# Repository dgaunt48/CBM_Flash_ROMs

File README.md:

# CBM_Flash_ROMs 
**Various Commodore Cartridge and ROM replacement projects.**

## 16BitFlashROM_Adaptor
Simple adaptor to use a 48 pin SMD flash rom in place of the AMIGA 500 dip rom.
Extra address pins on top to allow selection from multiple rom images.
[link to ibom](ibom_16BitFlashROM_Adaptor.html)

## C64_FlashCart
Flash cartridge for the C64

## FlashCartProgrammer
Flash Cart Programmer with sockets for VIC20 & C64 cartridges plus pin header for programming
of my 16Bit Flash ROM Adaptor board.
[link to ibom](FlashCartProgrammer/ibom.html)

## FlashSPI
Raspberry PI Pico code used to program the SPI Flash ROM on my FPGA boards.

## Vic20_DiagROM
Dissassembly of vc-20-diag.324173-01_blk5.bin.
Source file now assembles back into an identical image of the original Diag ROM file.

## Vic20_FlashCart
Vic20 Ram Expansion and Multi ROM Image Flash Cartridge.
[link to ibom](ibom_Vic20_FlashCart.html)

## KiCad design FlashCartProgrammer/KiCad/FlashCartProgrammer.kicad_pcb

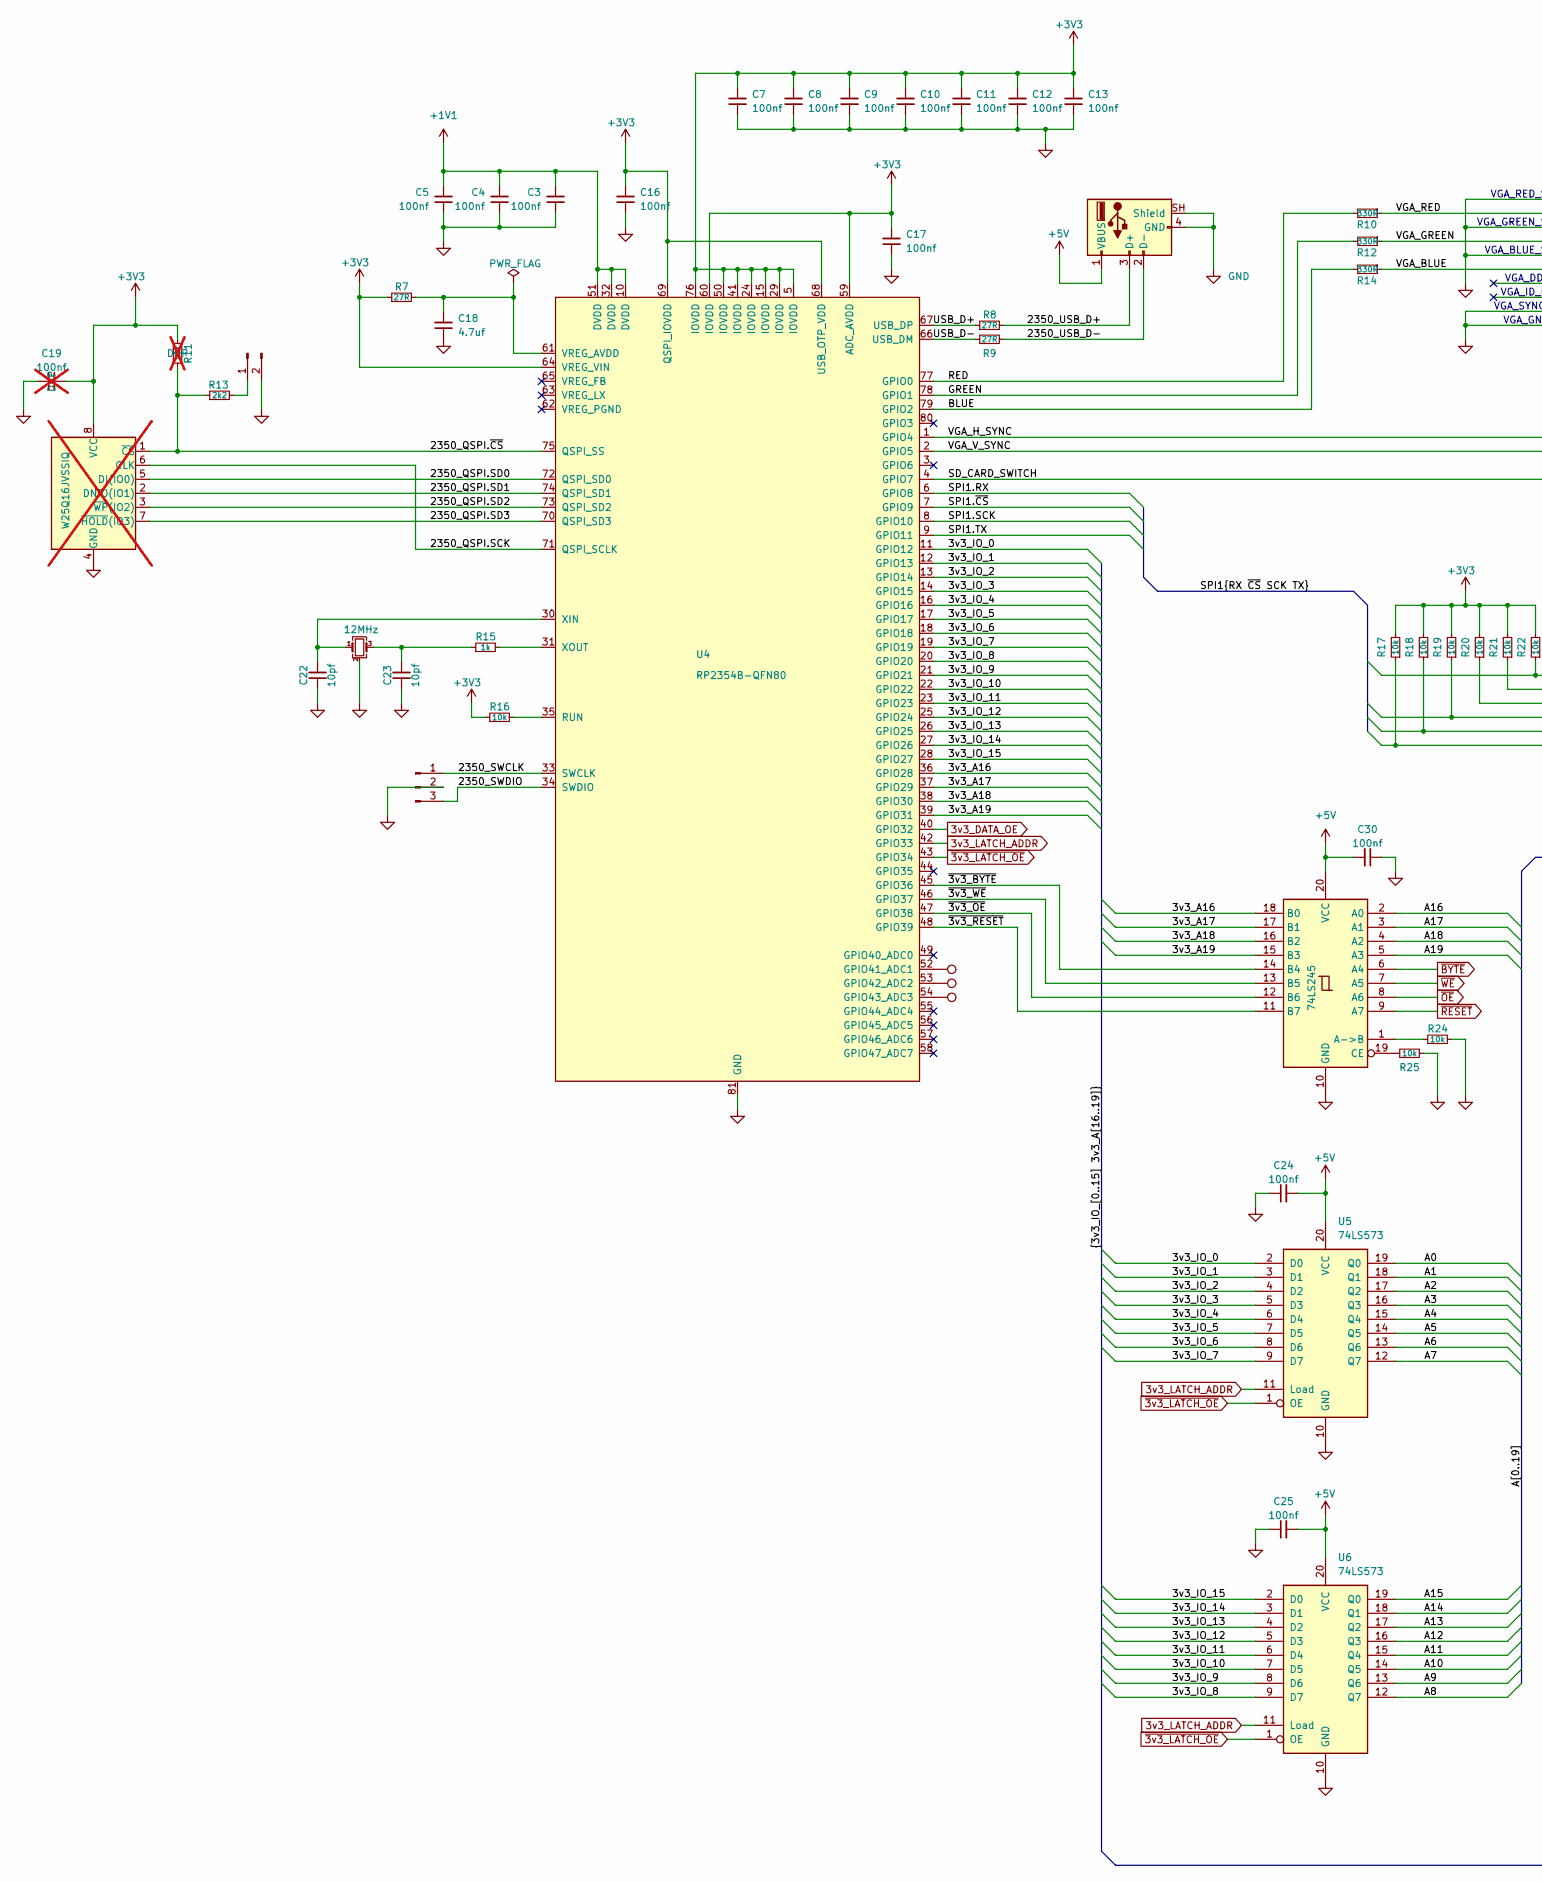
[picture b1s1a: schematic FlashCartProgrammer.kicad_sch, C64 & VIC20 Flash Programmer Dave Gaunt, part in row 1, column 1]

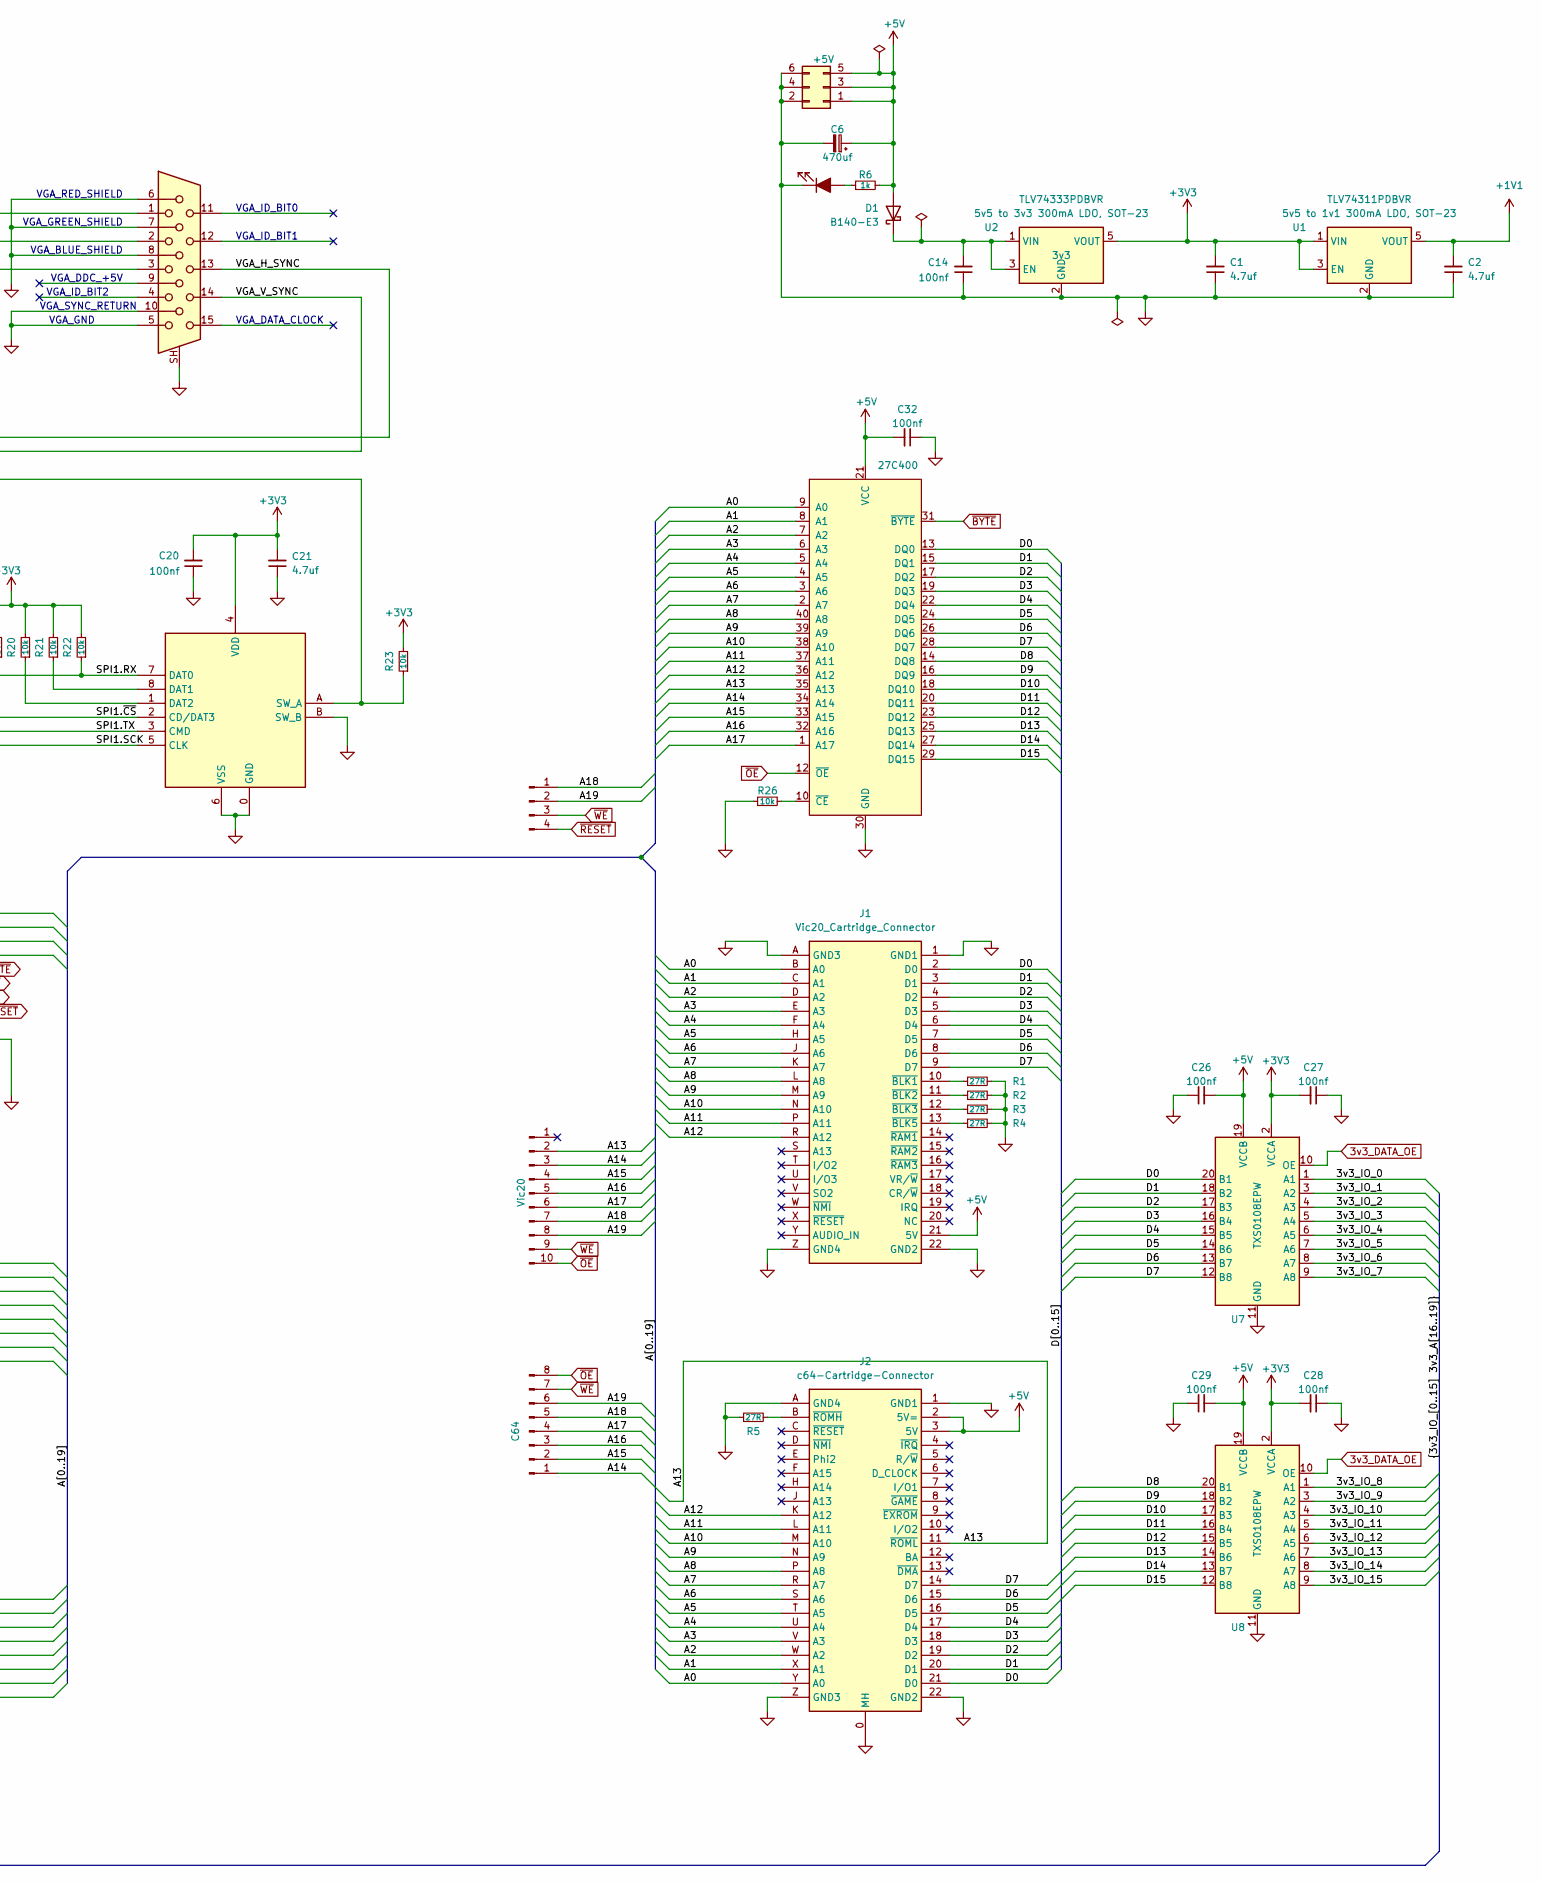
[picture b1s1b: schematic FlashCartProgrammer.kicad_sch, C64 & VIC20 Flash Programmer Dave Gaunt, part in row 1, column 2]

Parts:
C1, C2, C18, C21: 4.7uf; C_0603_1608Metric
C3, C4, C5, C7, C8, C9, C10, C11, C12, C13, C14, C16, C17, C20, C24, C25, C26, C27, C28, C29, C30, C32: 100nf; C_0603_1608Metric
C6: 470uf; CP_Radial_D5.0mm_P2.50mm
C19: 100nf; C_0603_1608Metric; not fitted
C22, C23: 10pf; C_0603_1608Metric
D1: B140-E3; D_SOD-123
J1: Vic20_Cartridge_Connector; Vic20-Cartridge-Connector; Mouser Part Number 587-307-044-558-201
J2: c64-Cartridge-Connector; Mouser Part Number 587-395-044-524-202
J3: +5V; PinHeader_2x03_P2.54mm_Vertical
J4: USB_A_KeyBoard; USB_A
J5: BOOT SEL; PinHeader_1x02_P2.54mm_Vertical
J6: DE15_Socket_HighDensity_MountingHoles; DSUB-15
J7: DM3D-SF; DM3DSF_SDCard; Mouser Part Number 798-DM3D-SF
J8: SWD; PinHeader_1x03_P2.54mm_Vertical
J9: C64; PinHeader_1x08_P2.54mm_Vertical
J10: Vic20; PinHeader_1x10_P2.54mm_Vertical
J11: ZIF; PinHeader_1x04_P2.54mm_Vertical
Power1: POWER; LED_0805_2012Metric
R1, R2, R3, R4, R5, R7, R8, R9: 27R; R_0603_1608Metric
R6, R15: 1k; R_0603_1608Metric
R10, R12, R14: 330R; R_0603_1608Metric
R11: 10k; R_0603_1608Metric; not fitted
R13: 2k2; R_0603_1608Metric
R16, R17, R18, R19, R20, R21, R22, R23, R24, R25, R26: 10k; R_0603_1608Metric
TP1, TP2, TP3: TestPoint; TestPoint_Pad_D1.0mm
U1: TLV74311PDBVR; SOT-23-5; Voltage 1v1
U2: TLV74333PDBVR; SOT-23-5; Voltage 3v3
U3: W25Q16JVSSIQ; SOIC-8_5.3x5.3mm_P1.27mm; not fitted
U4: RP2354B-QFN80; RP2350B_QFN-80_EP_10.573x10.573_Pitch0.4mm
U5, U6: 74LS573; TSSOP-20_4.4x6.5mm_P0.65mm
U7, U8: TXS0108EPW; TSSOP-20_4.4x6.5mm_P0.65mm
U10: 27C400; ZIF-40_W11.9_W12.7_W15.24_W17.78_W18.5_3M_240-1280-00-0602J
U18: 74LS245; TSSOP-20_4.4x6.5mm_P0.65mm
Y1: 12MHz; Crystal_SMD_SeikoEpson_FA238V-4Pin_3.2x2.5mm

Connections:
3v3_DATA_OE: U4.40 (GPIO32), U7.10 (OE), U8.10 (OE)
3v3_LATCH_ADDR: U4.42 (GPIO33), U5.11 (Load), U6.11 (Load)
+1V1: C2.2, C3.2, C4.2, C5.2, U1.5 (VOUT), U4.10 (DVDD), U4.32 (DVDD), U4.51 (DVDD)
+3V3: C1.2, C7.2, C8.2, C9.2, C10.2, C11.2, C12.2, C13.2, C16.2, C17.2, C19.2, C20.2, C21.2, C27.2, C28.2, J7.4 (VDD), R7.1, R11.1, R16.1, R17.2, R18.2, R19.2, R20.2, R21.2, R22.2, R23.2, U1.1 (VIN), U1.3 (EN), U2.5 (VOUT), U3.8 (VCC), U4.5 (IOVDD), U4.15 (IOVDD), U4.24 (IOVDD), U4.29 (IOVDD), U4.41 (IOVDD), U4.50 (IOVDD), U4.59 (ADC_AVDD), U4.60 (IOVDD), U4.64 (VREG_VIN), U4.68 (USB_OTP_VDD), U4.69 (QSPI_IOVDD), U4.76 (IOVDD), U7.2 (VCCA), U8.2 (VCCA)
+5V: C6.1, C24.2, C25.2, C26.2, C29.2, C30.2, C32.2, D1.2 (A), J1.21 (5V), J2.2 (5V=), J2.3 (5V), J3.1, J3.3, J3.5, J4.1 (VBUS), R6.2, U5.20 (VCC), U6.20 (VCC), U7.19 (VCCB), U8.19 (VCCB), U10.21 (VCC), U18.20 (VCC)
/3v3_A16: U4.36 (GPIO28), U18.18 (B0)
/3v3_A17: U4.37 (GPIO29), U18.17 (B1)
/3v3_A18: U4.38 (GPIO30), U18.16 (B2)
/3v3_A19: U4.39 (GPIO31), U18.15 (B3)
/3v3_IO_0: U4.11 (GPIO12), U5.2 (D0), U7.1 (A1)
/3v3_IO_1: U4.12 (GPIO13), U5.3 (D1), U7.3 (A2)
/3v3_IO_2: U4.13 (GPIO14), U5.4 (D2), U7.4 (A3)
/3v3_IO_3: U4.14 (GPIO15), U5.5 (D3), U7.5 (A4)
/3v3_IO_4: U4.16 (GPIO16), U5.6 (D4), U7.6 (A5)
/3v3_IO_5: U4.17 (GPIO17), U5.7 (D5), U7.7 (A6)
/3v3_IO_6: U4.18 (GPIO18), U5.8 (D6), U7.8 (A7)
/3v3_IO_7: U4.19 (GPIO19), U5.9 (D7), U7.9 (A8)
/3v3_IO_8: U4.20 (GPIO20), U6.9 (D7), U8.1 (A1)
/3v3_IO_9: U4.21 (GPIO21), U6.8 (D6), U8.3 (A2)
/3v3_IO_10: U4.22 (GPIO22), U6.7 (D5), U8.4 (A3)
/3v3_IO_11: U4.23 (GPIO23), U6.6 (D4), U8.5 (A4)
/3v3_IO_12: U4.25 (GPIO24), U6.5 (D3), U8.6 (A5)
/3v3_IO_13: U4.26 (GPIO25), U6.4 (D2), U8.7 (A6)
/3v3_IO_14: U4.27 (GPIO26), U6.3 (D1), U8.8 (A7)
/3v3_IO_15: U4.28 (GPIO27), U6.2 (D0), U8.9 (A8)
/2350_QSPI.SCK: U3.6 (CLK), U4.71 (QSPI_SCLK)
/2350_QSPI.SD0: U3.5 (DI(IO0)), U4.72 (QSPI_SD0)
/2350_QSPI.SD1: U3.2 (DO(IO1)), U4.74 (QSPI_SD1)
/2350_QSPI.SD2: U3.3 (~WP(IO2)), U4.73 (QSPI_SD2)
/2350_QSPI.SD3: U3.7 (~HOLD(IO3)), U4.70 (QSPI_SD3)
/2350_QSPI.~CS: R11.2, R13.1, U3.1 (~CS), U4.75 (QSPI_SS)
/2350_SWCLK: J8.1, U4.33 (SWCLK)
/2350_SWDIO: J8.3, U4.34 (SWDIO)
/2350_USB_D+: J4.3 (D+), R8.2
/2350_USB_D-: J4.2 (D-), R9.2
/A0: J1.B (A0), J2.Y (A0), U5.19 (Q0), U10.9 (A0)
/A1: J1.C (A1), J2.X (A1), U5.18 (Q1), U10.8 (A1)
/A2: J1.D (A2), J2.W (A2), U5.17 (Q2), U10.7 (A2)
/A3: J1.E (A3), J2.V (A3), U5.16 (Q3), U10.6 (A3)
/A4: J1.F (A4), J2.U (A4), U5.15 (Q4), U10.5 (A4)
/A5: J1.H (A5), J2.T (A5), U5.14 (Q5), U10.4 (A5)
/A6: J1.J (A6), J2.S (A6), U5.13 (Q6), U10.3 (A6)
/A7: J1.K (A7), J2.R (A7), U5.12 (Q7), U10.2 (A7)
/A8: J1.L (A8), J2.P (A8), U6.12 (Q7), U10.40 (A8)
/A9: J1.M (A9), J2.N (A9), U6.13 (Q6), U10.39 (A9)
/A10: J1.N (A10), J2.M (A10), U6.14 (Q5), U10.38 (A10)
/A11: J1.P (A11), J2.L (A11), U6.15 (Q4), U10.37 (A11)
/A12: J1.R (A12), J2.K (A12), U6.16 (Q3), U10.36 (A12)
/A13: J2.11 (~ROML), J10.2, U6.17 (Q2), U10.35 (A13)
/A14: J9.1, J10.3, U6.18 (Q1), U10.34 (A14)
/A15: J9.2, J10.4, U6.19 (Q0), U10.33 (A15)
/A16: J9.3, J10.5, U10.32 (A16), U18.2 (A0)
/A17: J9.4, J10.6, U10.1 (A17), U18.3 (A1)
/A18: J9.5, J10.7, J11.1, U18.4 (A2)
/A19: J9.6, J10.8, J11.2, U18.5 (A3)
/BLUE: R14.2, U4.79 (GPIO2)
/D0: J1.2 (D0), J2.21 (D0), U7.20 (B1), U10.13 (DQ0)
/D1: J1.3 (D1), J2.20 (D1), U7.18 (B2), U10.15 (DQ1)
/D2: J1.4 (D2), J2.19 (D2), U7.17 (B3), U10.17 (DQ2)
/D3: J1.5 (D3), J2.18 (D3), U7.16 (B4), U10.19 (DQ3)
/D4: J1.6 (D4), J2.17 (D4), U7.15 (B5), U10.22 (DQ4)
/D5: J1.7 (D5), J2.16 (D5), U7.14 (B6), U10.24 (DQ5)
/D6: J1.8 (D6), J2.15 (D6), U7.13 (B7), U10.26 (DQ6)
/D7: J1.9 (D7), J2.14 (D7), U7.12 (B8), U10.28 (DQ7)
/D8: U8.20 (B1), U10.14 (DQ8)
/D9: U8.18 (B2), U10.16 (DQ9)
/D10: U8.17 (B3), U10.18 (DQ10)
/D11: U8.16 (B4), U10.20 (DQ11)
/D12: U8.15 (B5), U10.23 (DQ12)
/D13: U8.14 (B6), U10.25 (DQ13)
/D14: U8.13 (B7), U10.27 (DQ14)
/D15: U8.12 (B8), U10.29 (DQ15)
/GREEN: R12.2, U4.78 (GPIO1)
/RED: R10.2, U4.77 (GPIO0)
/SD_CARD_SWITCH: J7.A (SW_A), R23.1, U4.4 (GPIO7)
/SPI1.RX: J7.7 (DAT0), R22.1, U4.6 (GPIO8)
/SPI1.SCK: J7.5 (CLK), R17.1, U4.8 (GPIO10)
/SPI1.TX: J7.3 (CMD), R18.1, U4.9 (GPIO11)
/SPI1.~CS: J7.2 (CD/DAT3), R19.1, U4.7 (GPIO9)
/USB_D+: R8.1, U4.67 (USB_DP)
/USB_D-: R9.1, U4.66 (USB_DM)
/VGA_BLUE: J6.3, R14.1
/VGA_GREEN: J6.2, R12.1
/VGA_H_SYNC: J6.13, U4.1 (GPIO4)
/VGA_RED: J6.1, R10.1
/VGA_V_SYNC: J6.14, U4.2 (GPIO5)
/~3v3_BYTE: U4.45 (GPIO36), U18.14 (B4)
/~3v3_OE: U4.47 (GPIO38), U18.12 (B6)
/~3v3_RESET: U4.48 (GPIO39), U18.11 (B7)
/~3v3_WE: U4.46 (GPIO37), U18.13 (B5)
GND: C1.1, C2.1, C3.1, C4.1, C5.1, C6.2, C7.1, C8.1, C9.1, C10.1, C11.1, C12.1, C13.1, C14.1, C16.1, C17.1, C18.1, C19.1, C20.1, C21.1, C22.1, C23.1, C24.1, C25.1, C26.1, C27.1, C28.1, C29.1, C30.1, C32.1, J1.1 (GND1), J1.22 (GND2), J1.A (GND3), J1.Z (GND4), J2.0 (MH), J2.1 (GND1), J2.22 (GND2), J2.A (GND4), J2.Z (GND3), J3.2, J3.4, J3.6, J4.4 (GND), J4.SH (Shield), J5.2, J6.5, J6.6, J6.7, J6.8, J6.10, J6.SH, J7.0 (GND), J7.6 (VSS), J7.B (SW_B), J8.2, Power1.1 (K), R1.2, R2.2, R3.2, R4.2, R5.1, R24.2, R25.2, R26.1, U1.2 (GND), U2.2 (GND), U3.4 (GND), U4.81 (GND), U5.10 (GND), U6.10 (GND), U7.11 (GND), U8.11 (GND), U10.11 (GND), U10.30 (GND), U18.10 (GND), Y1.2 (G), Y1.4 (G)
unnamed: C23.2, R15.1, Y1.3
unnamed: C14.2, D1.1 (K), U2.1 (VIN), U2.3 (EN)
unnamed: J1.10 (~BLK1), R1.1
unnamed: J1.11 (~BLK2), R2.1
unnamed: J1.12 (~BLK3), R3.1
unnamed: J1.13 (~BLK5), R4.1
unnamed: J2.B (~ROMH), R5.2
unnamed: J5.1, R13.2
unnamed: J7.8 (DAT1), R21.1
unnamed: J7.1 (DAT2), R20.1
unnamed: Power1.2 (A), R6.1
unnamed: TP1.1 (1_1), U4.52 (GPIO41_ADC1)
unnamed: TP2.1 (1_1), U4.53 (GPIO42_ADC2)
unnamed: TP3.1 (1_1), U4.54 (GPIO43_ADC3)
unnamed: R16.2, U4.35 (RUN)
unnamed: C18.2, R7.2, U4.61 (VREG_AVDD)
unnamed: C22.2, U4.30 (XIN), Y1.1
unnamed: R15.2, U4.31 (XOUT)
unnamed: R26.2, U10.10 (~CE)
unnamed: R24.1, U18.1 (A->B)
unnamed: R25.1, U18.19 (CE)
~3v3_LATCH_OE: U4.43 (GPIO34), U5.1 (OE), U6.1 (OE)
~BYTE: U10.31 (~BYTE), U18.6 (A4)
~OE: J9.8, J10.10, U10.12 (~OE), U18.8 (A6)
~RESET: J11.4, U18.9 (A7)
~WE: J9.7, J10.9, J11.3, U18.7 (A5)

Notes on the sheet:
VGA_ID_BIT1
VGA_DATA_CLOCK
VGA_ID_BIT2
VGA_GND
VGA_SYNC_RETURN
VGA_ID_BIT0
VGA_BLUE_SHIELD
VGA_RED_SHIELD
VGA_DDC_+5V
VGA_GREEN_SHIELD

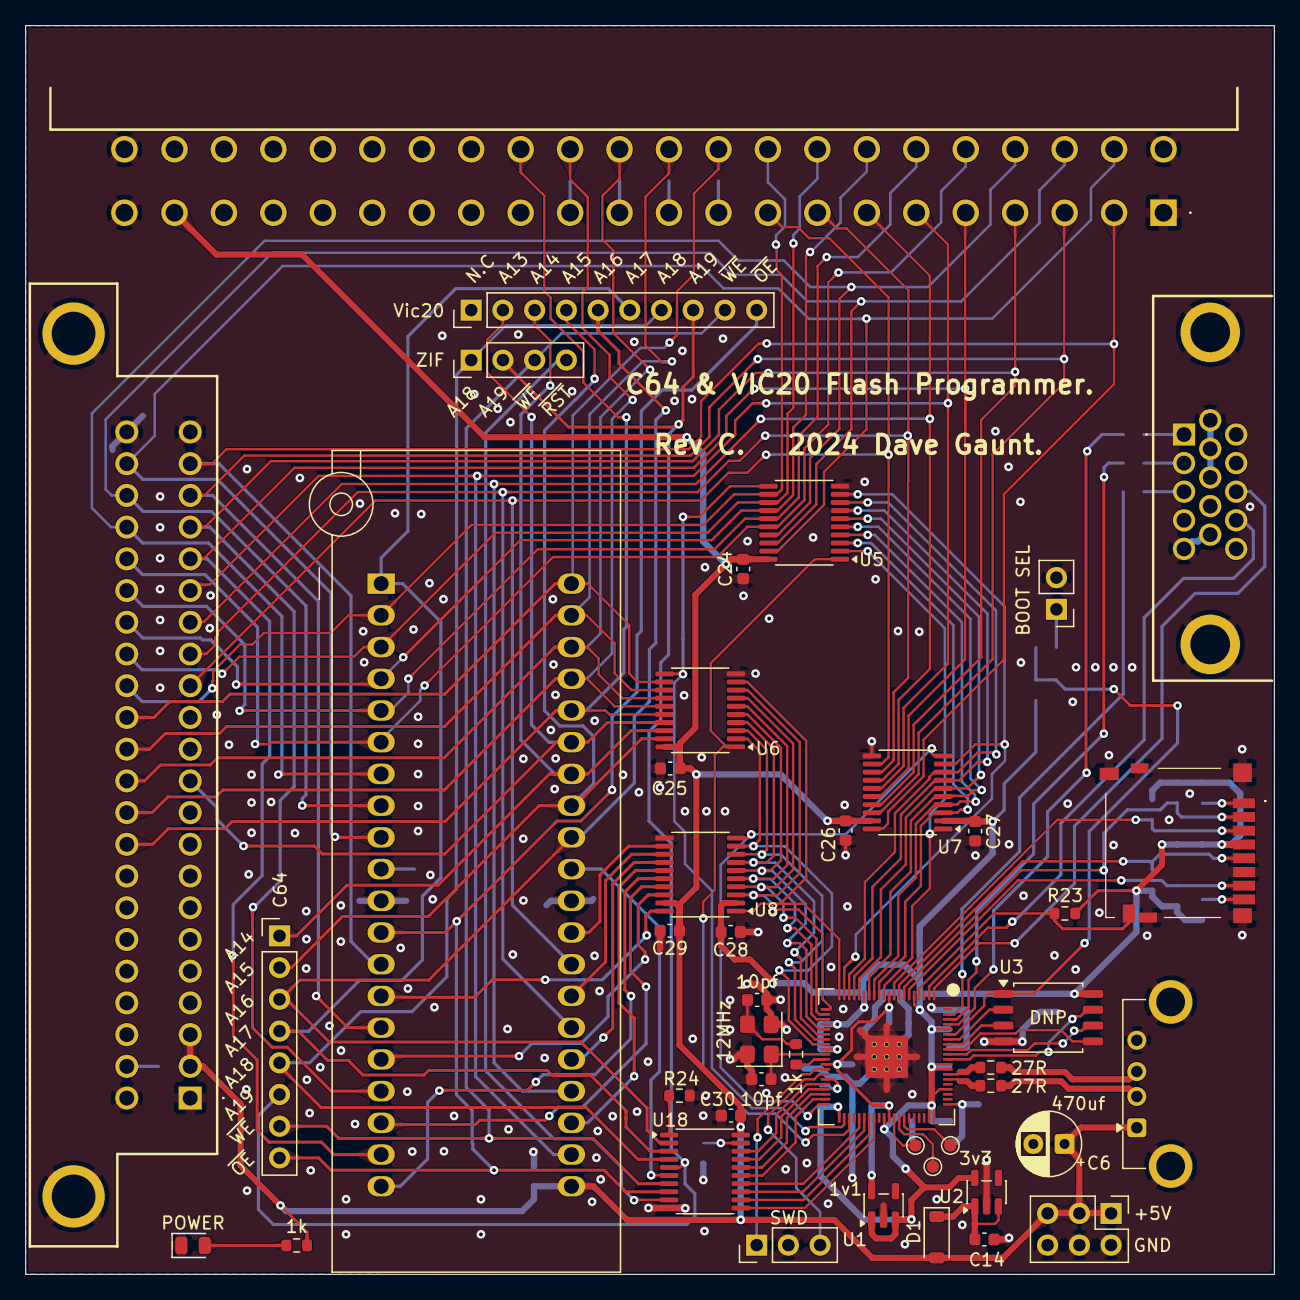
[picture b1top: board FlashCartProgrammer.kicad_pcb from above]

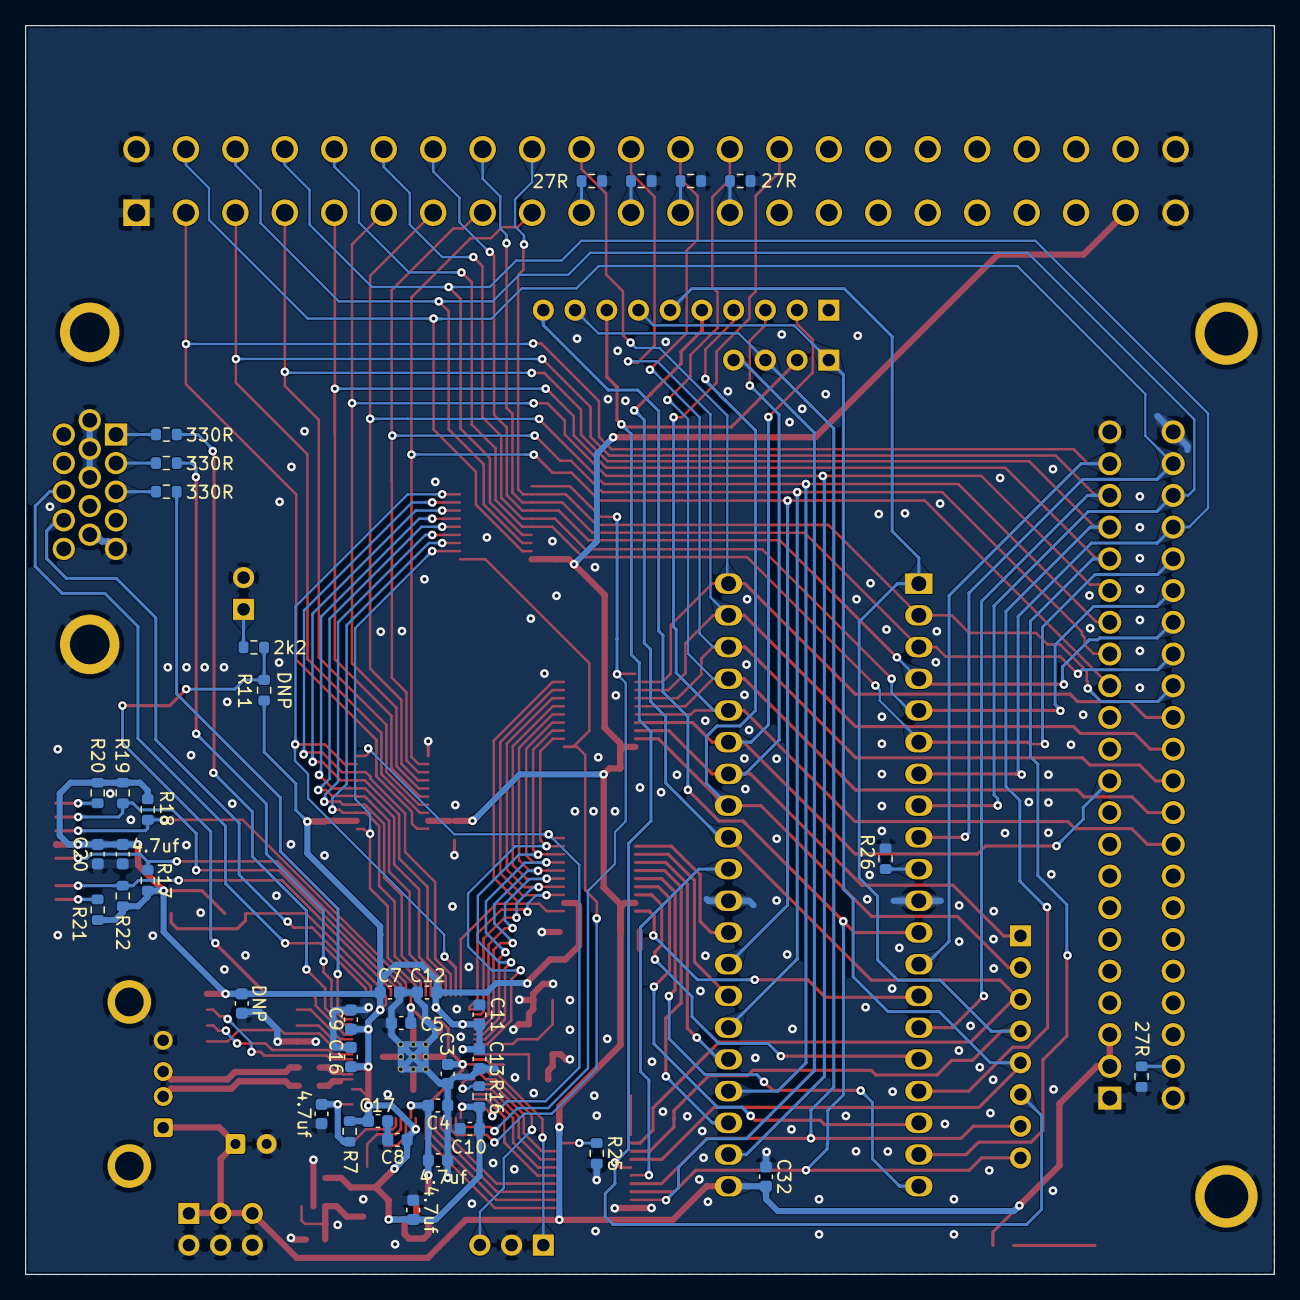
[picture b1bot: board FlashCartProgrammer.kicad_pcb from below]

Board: 2 copper layers, 100.0 x 100.0 mm, 83 parts (39 on the bottom side), 117 nets.

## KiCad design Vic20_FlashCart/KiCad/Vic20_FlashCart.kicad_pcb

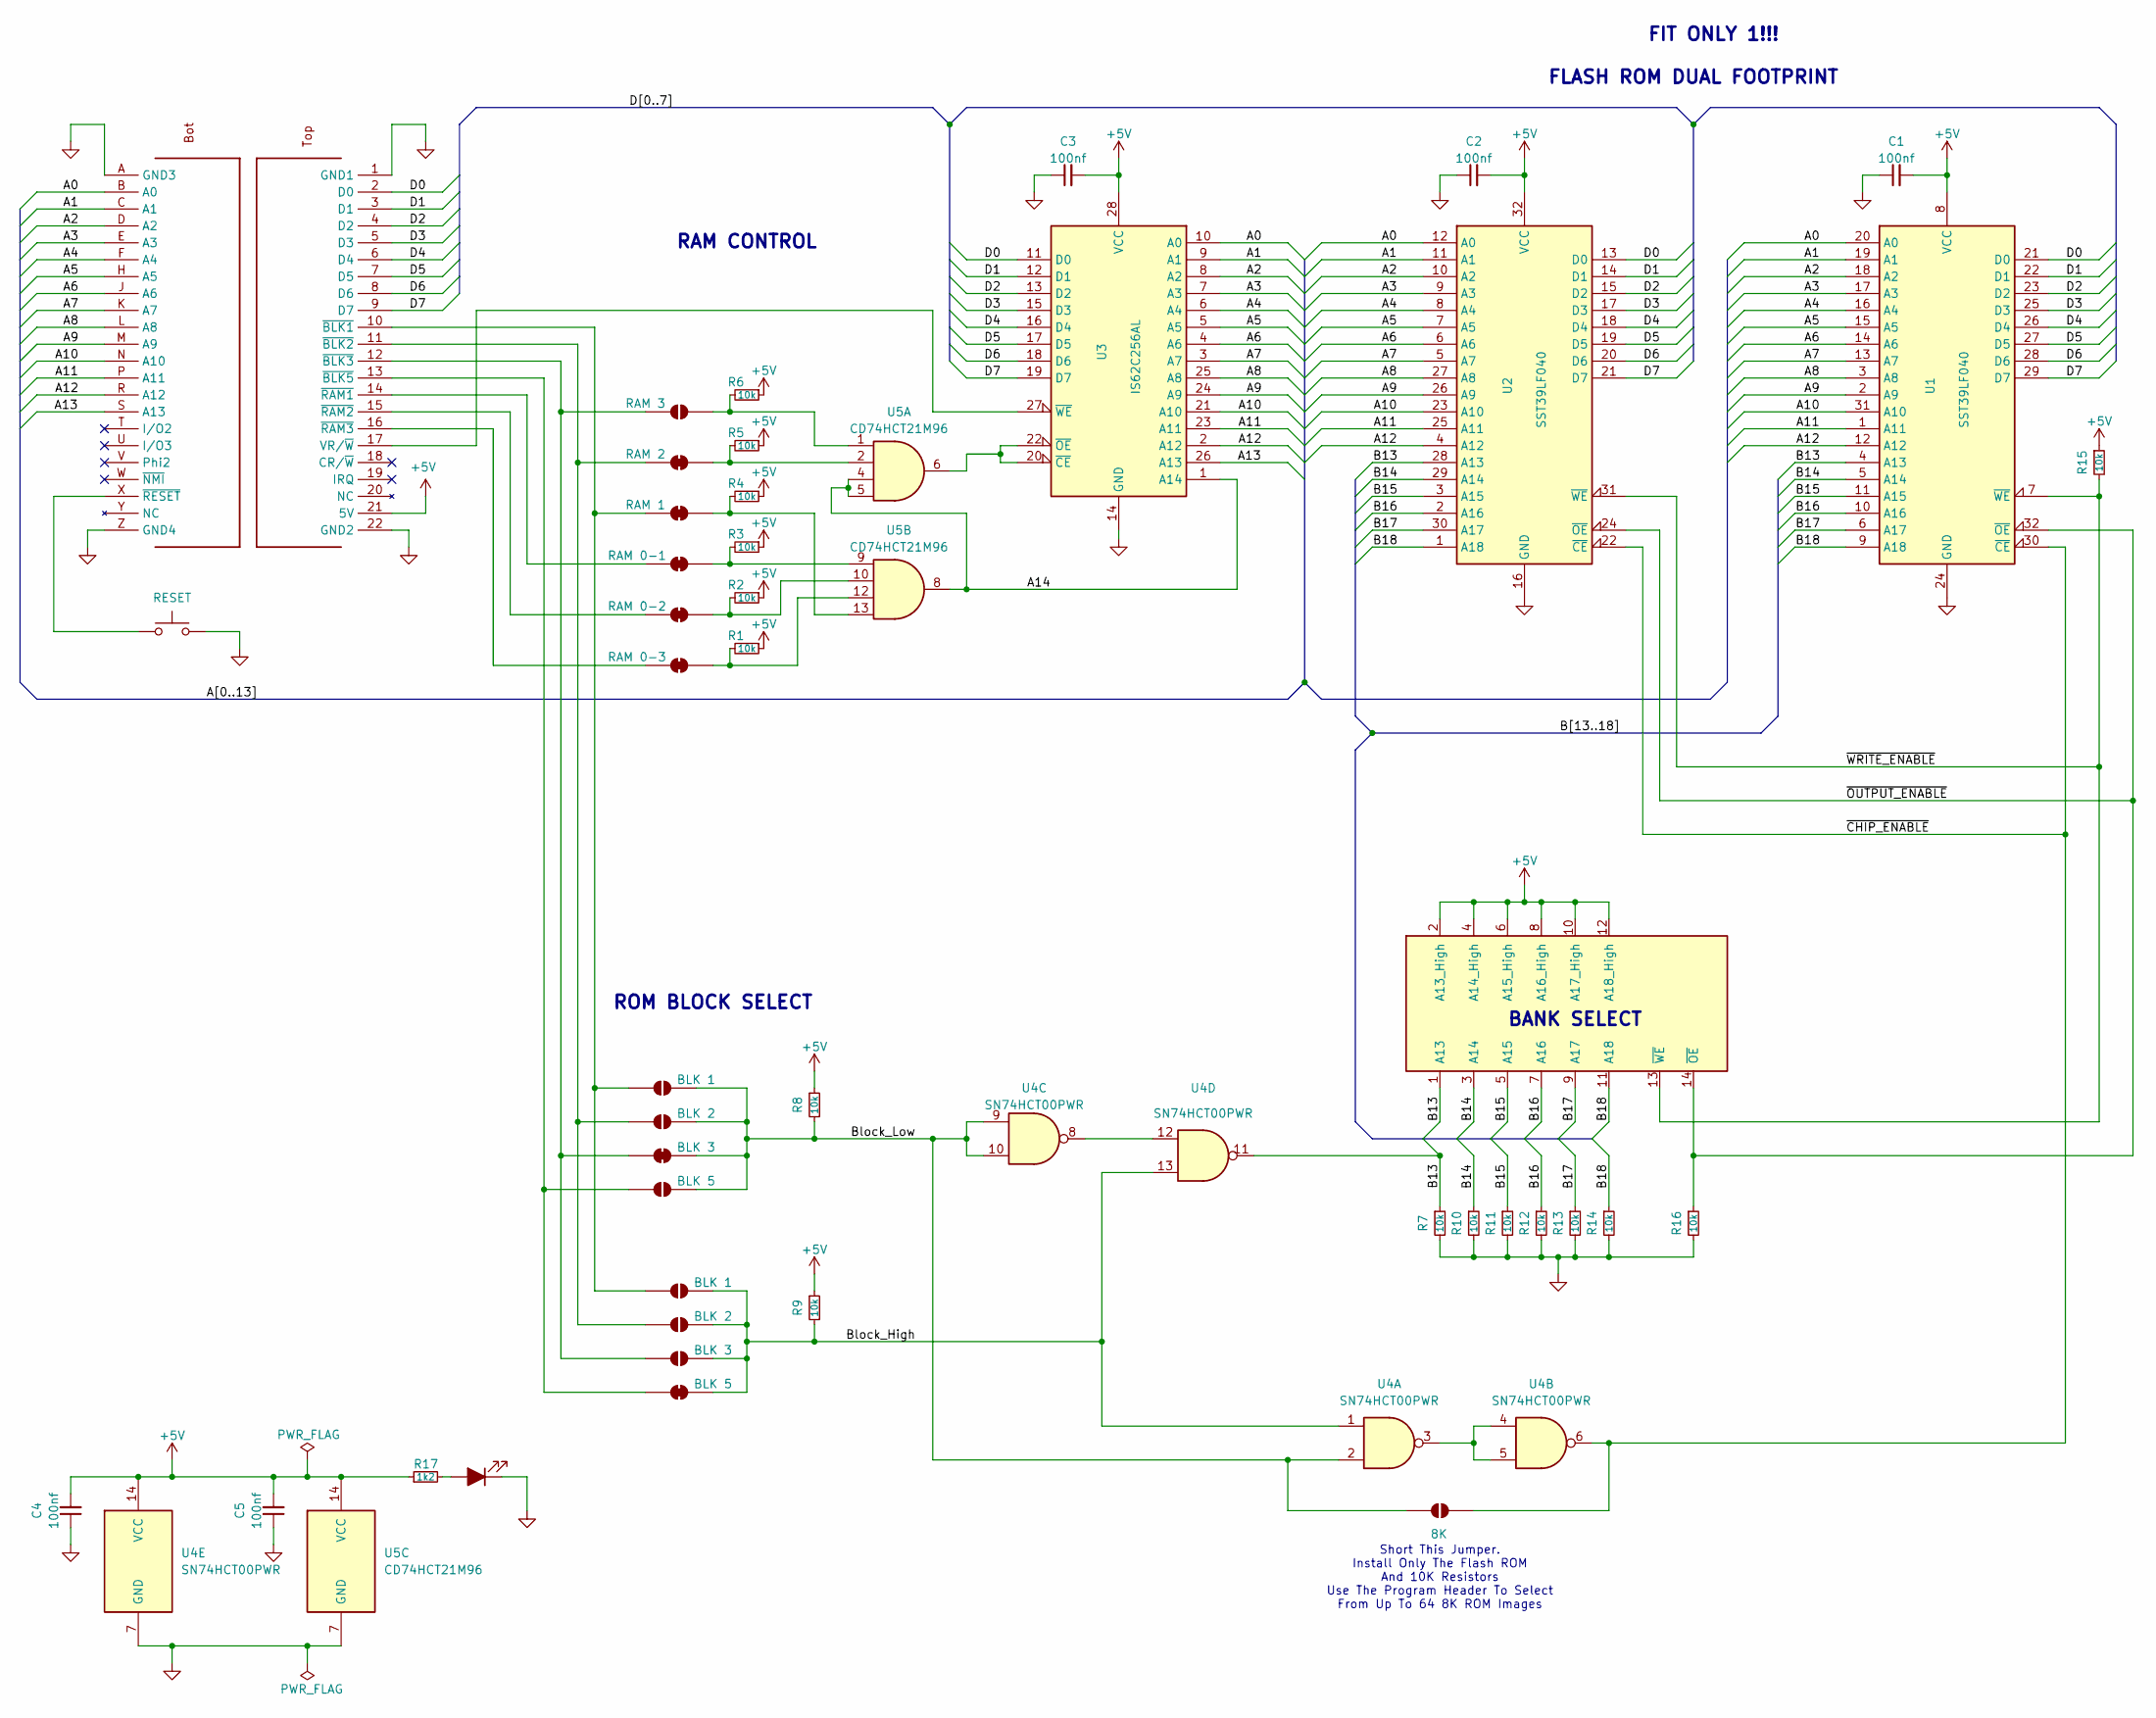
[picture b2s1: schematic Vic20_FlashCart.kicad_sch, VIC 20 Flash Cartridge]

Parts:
C1, C2, C3, C4, C5: 100nf; C_0603_1608Metric
J3: Pin Headers; PinHeader_Vic20_Cartridge
JP1: RAM 0-1; SolderJumper-2_P1.3mm_Bridged2Bar_RoundedPad1.0x1.5mm
JP2: RAM 0-2; SolderJumper-2_P1.3mm_Bridged2Bar_RoundedPad1.0x1.5mm
JP3: RAM 0-3; SolderJumper-2_P1.3mm_Bridged2Bar_RoundedPad1.0x1.5mm
JP4: RAM 1; SolderJumper-2_P1.3mm_Bridged2Bar_RoundedPad1.0x1.5mm
JP5: RAM 3; SolderJumper-2_P1.3mm_Open_RoundedPad1.0x1.5mm
JP6: RAM 2; SolderJumper-2_P1.3mm_Bridged2Bar_RoundedPad1.0x1.5mm
JP7, JP11: BLK 1; SolderJumper-2_P1.3mm_Open_RoundedPad1.0x1.5mm
JP8, JP12: BLK 2; SolderJumper-2_P1.3mm_Open_RoundedPad1.0x1.5mm
JP9: BLK 3; SolderJumper-2_P1.3mm_Bridged2Bar_RoundedPad1.0x1.5mm
JP10: BLK 5; SolderJumper-2_P1.3mm_Open_RoundedPad1.0x1.5mm
JP13: BLK 3; SolderJumper-2_P1.3mm_Open_RoundedPad1.0x1.5mm
JP14: BLK 5; SolderJumper-2_P1.3mm_Bridged2Bar_RoundedPad1.0x1.5mm
JP16: 8K; SolderJumper-2_P1.3mm_Open_RoundedPad1.0x1.5mm
Power1: POWER; LEDC2012X90N
R1, R2, R3, R4, R5, R6, R7, R8, R9, R10, R11, R12, R13, R14, R15, R16: 10k; R_0603_1608Metric
R17: 1k2; R_0603_1608Metric
S1: RESET; SW_PUSH_6mm_H4.3mm; Mouser Part Number 653-B3F-1052-G
U1: SST39LF040; TSOP-I-32_12.4x8mm_P0.5mm
U2: SST39LF040; PLCC-32_11.4x14.0mm_P1.27mm
U3: IS62C256AL; TSOP-I-28_(PIN 1 CENTRE)_11.8x8mm_P0.55mm
U4: SN74HCT00PWR; TSSOP-14_4.4x5mm_P0.65mm
U5: CD74HCT21M96; SOIC-14_3.9x8.7mm_P1.27mm
X1: Cart Fingers; VIC20-Cart-Num

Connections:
+5V: C1.2, C2.2, C3.2, C4.2, C5.2, J3.2 (A13_High), J3.4 (A14_High), J3.6 (A15_High), J3.8 (A16_High), J3.10 (A17_High), J3.12 (A18_High), R1.1, R2.1, R3.1, R4.1, R5.1, R6.1, R8.1, R9.1, R15.1, R17.1, U1.8 (VCC), U2.32 (VCC), U3.28 (VCC), U4.14 (VCC), U5.14 (VCC), X1.21 (5V)
/A0: U1.20 (A0), U2.12 (A0), U3.10 (A0), X1.B (A0)
/A1: U1.19 (A1), U2.11 (A1), U3.9 (A1), X1.C (A1)
/A2: U1.18 (A2), U2.10 (A2), U3.8 (A2), X1.D (A2)
/A3: U1.17 (A3), U2.9 (A3), U3.7 (A3), X1.E (A3)
/A4: U1.16 (A4), U2.8 (A4), U3.6 (A4), X1.F (A4)
/A5: U1.15 (A5), U2.7 (A5), U3.5 (A5), X1.H (A5)
/A6: U1.14 (A6), U2.6 (A6), U3.4 (A6), X1.J (A6)
/A7: U1.13 (A7), U2.5 (A7), U3.3 (A7), X1.K (A7)
/A8: U1.3 (A8), U2.27 (A8), U3.25 (A8), X1.L (A8)
/A9: U1.2 (A9), U2.26 (A9), U3.24 (A9), X1.M (A9)
/A10: U1.31 (A10), U2.23 (A10), U3.21 (A10), X1.N (A10)
/A11: U1.1 (A11), U2.25 (A11), U3.23 (A11), X1.P (A11)
/A12: U1.12 (A12), U2.4 (A12), U3.2 (A12), X1.R (A12)
/A13: U3.26 (A13), X1.S (A13)
/A14: U3.1 (A14), U5.4, U5.5, U5.8
/B13: J3.1 (A13), R7.1, U1.4 (A13), U2.28 (A13), U4.11
/B14: J3.3 (A14), R10.1, U1.5 (A14), U2.29 (A14)
/B15: J3.5 (A15), R11.1, U1.11 (A15), U2.3 (A15)
/B16: J3.7 (A16), R12.1, U1.10 (A16), U2.2 (A16)
/B17: J3.9 (A17), R13.1, U1.6 (A17), U2.30 (A17)
/B18: J3.11 (A18), R14.1, U1.9 (A18), U2.1 (A18)
/Block_High: JP11.2 (B), JP12.2 (B), JP13.2 (B), JP14.2 (B), R9.2, U4.1, U4.13
/Block_Low: JP7.2 (B), JP8.2 (B), JP9.2 (B), JP10.2 (B), JP16.1 (A), R8.2, U4.2, U4.9, U4.10
/D0: U1.21 (D0), U2.13 (D0), U3.11 (D0), X1.2 (D0)
/D1: U1.22 (D1), U2.14 (D1), U3.12 (D1), X1.3 (D1)
/D2: U1.23 (D2), U2.15 (D2), U3.13 (D2), X1.4 (D2)
/D3: U1.25 (D3), U2.17 (D3), U3.15 (D3), X1.5 (D3)
/D4: U1.26 (D4), U2.18 (D4), U3.16 (D4), X1.6 (D4)
/D5: U1.27 (D5), U2.19 (D5), U3.17 (D5), X1.7 (D5)
/D6: U1.28 (D6), U2.20 (D6), U3.18 (D6), X1.8 (D6)
/D7: U1.29 (D7), U2.21 (D7), U3.19 (D7), X1.9 (D7)
/~CHIP_ENABLE: JP16.2 (B), U1.30 (~CE), U2.22 (~CE), U4.6
/~OUTPUT_ENABLE: J3.14 (~OE), R16.1, U1.32 (~OE), U2.24 (~OE)
/~WRITE_ENABLE: J3.13 (~WE), R15.2, U1.7 (~WE), U2.31 (~WE)
GND: C1.1, C2.1, C3.1, C4.1, C5.1, Power1.1 (K), R7.2, R10.2, R11.2, R12.2, R13.2, R14.2, R16.2, S1.2, U1.24 (GND), U2.16 (GND), U3.14 (GND), U4.7 (GND), U5.7 (GND), X1.1 (GND1), X1.22 (GND2), X1.A (GND3), X1.Z (GND4)
unnamed: JP1.1 (A), X1.14 (~RAM1)
unnamed: JP1.2 (B), R3.2, U5.9
unnamed: JP2.1 (A), X1.15 (~RAM2)
unnamed: JP2.2 (B), R2.2, U5.10
unnamed: JP3.1 (A), X1.16 (~RAM3)
unnamed: JP3.2 (B), R1.2, U5.12
unnamed: JP4.2 (B), R4.2, U5.13
unnamed: JP5.2 (B), R6.2, U5.1
unnamed: JP6.2 (B), R5.2, U5.2
unnamed: JP10.1 (A), JP14.1 (A), X1.13 (~BLK5)
unnamed: JP4.1 (A), JP7.1 (A), JP11.1 (A), X1.10 (~BLK1)
unnamed: JP6.1 (A), JP8.1 (A), JP12.1 (A), X1.11 (~BLK2)
unnamed: JP5.1 (A), JP9.1 (A), JP13.1 (A), X1.12 (~BLK3)
unnamed: Power1.2 (A), R17.2
unnamed: U3.20 (~CE), U3.22 (~OE), U5.6
unnamed: U3.27 (~WE), X1.17 (VR/~W)
unnamed: U4.3, U4.4, U4.5
unnamed: U4.8, U4.12
unnamed: S1.1, X1.X (~RESET)

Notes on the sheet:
BANK SELECT
FIT ONLY 1!!! FLASH ROM DUAL FOOTPRINT
ROM BLOCK SELECT
Short This Jumper. Install Only The Flash ROM And 10K Resistors Use The Program Header To Select From Up To 64 8K ROM Images
RAM CONTROL

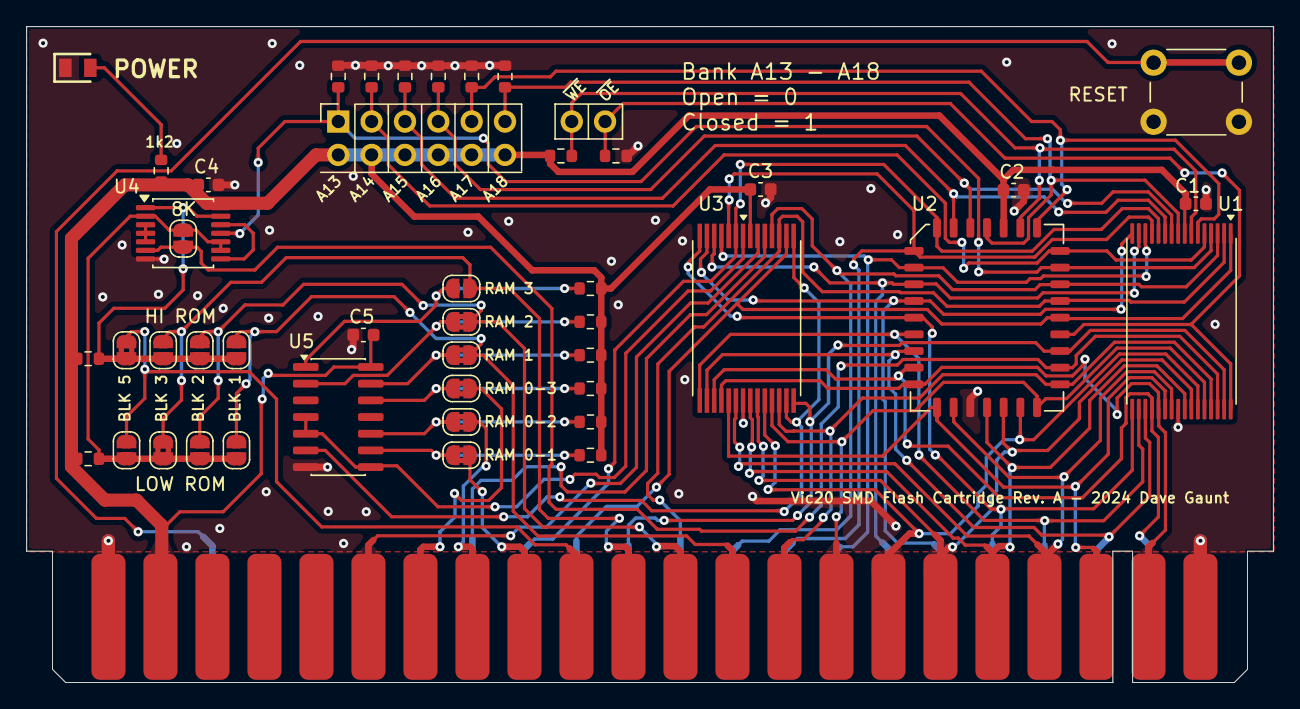
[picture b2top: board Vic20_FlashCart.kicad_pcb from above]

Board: 2 copper layers, 94.9 x 50.0 mm, 46 parts (0 on the bottom side), 55 nets.
